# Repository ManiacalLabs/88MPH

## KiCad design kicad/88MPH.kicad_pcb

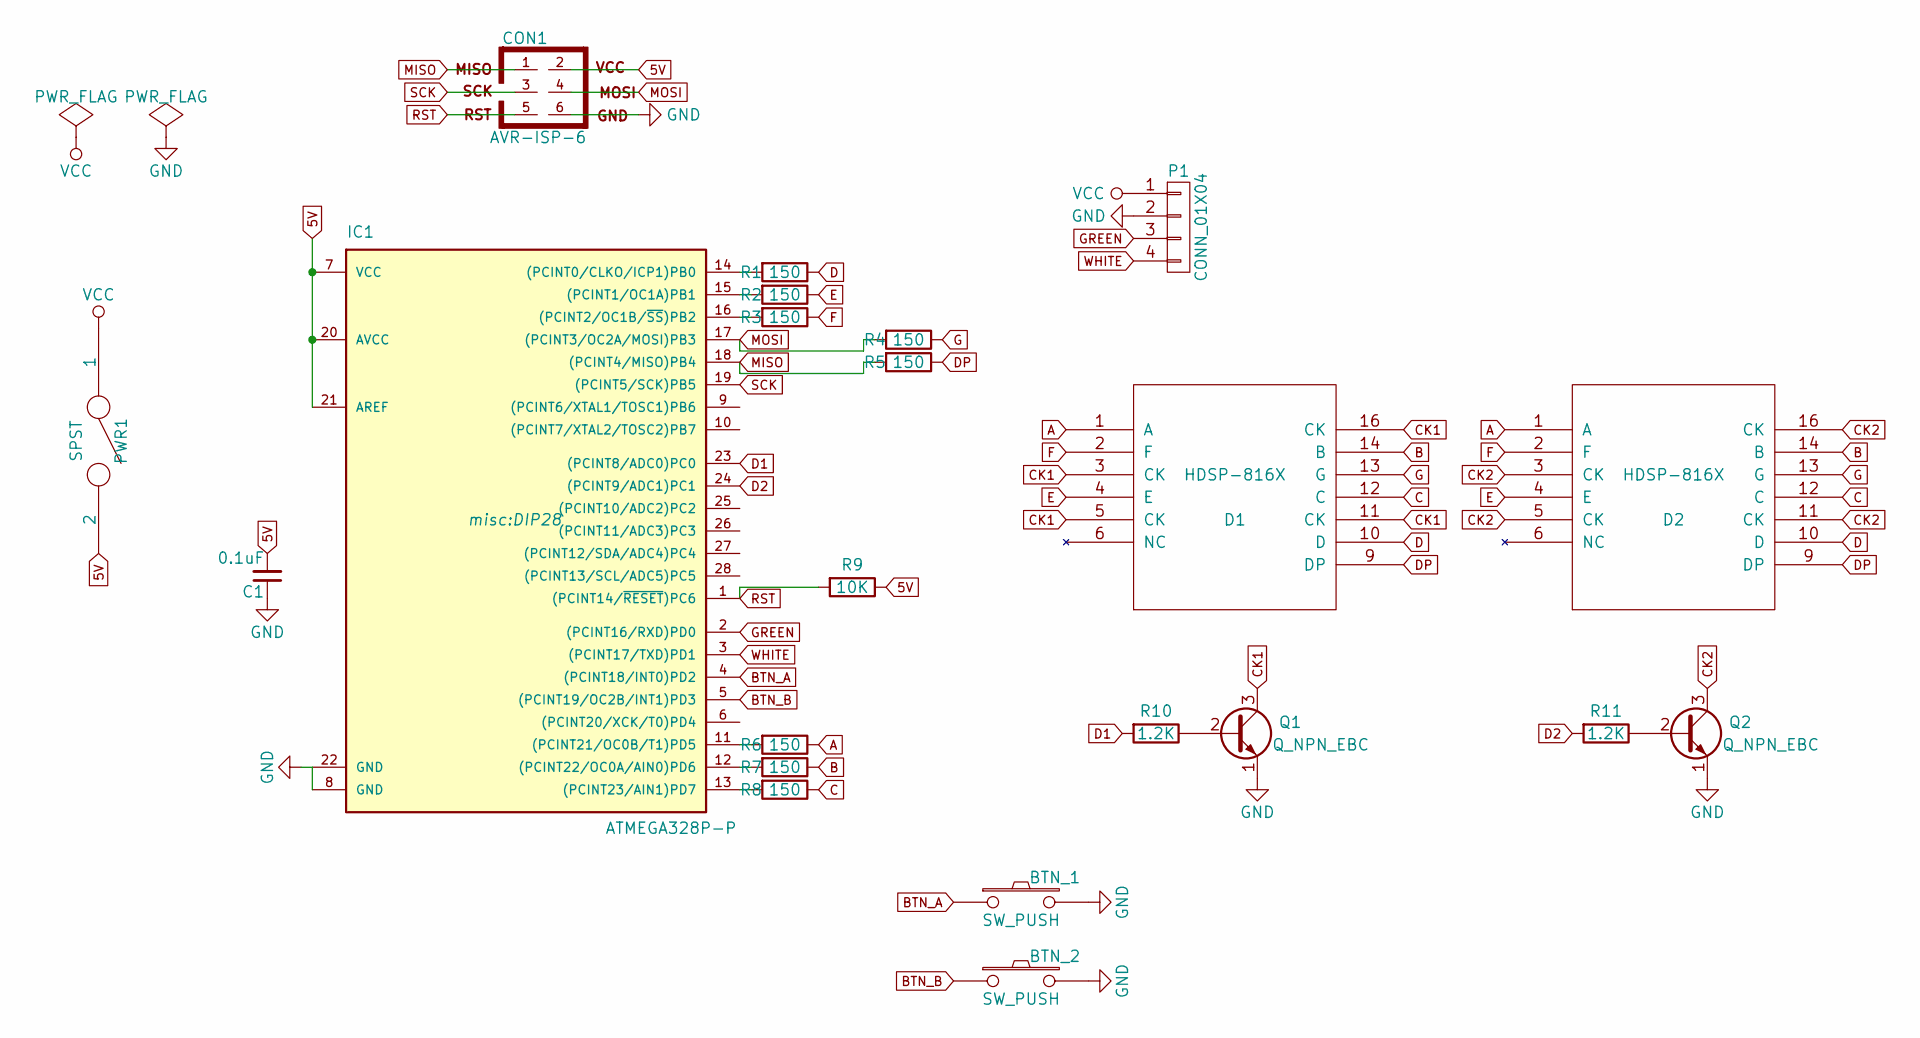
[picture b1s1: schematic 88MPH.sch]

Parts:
BTN_1, BTN_2: SW_PUSH; SW_PUSH_6mm
C1: 0.1uF; C_Disc_D3_P2.5
CON1: AVR-ISP-6; ICSP
D1, D2: HDSP-816X
IC1: ATMEGA328P-P; DIP28
P1: CONN_01X04; Strip_1x04
PWR1: SPST; SW_Micro_SPST
Q1, Q2: Q_NPN_EBC; TO-92_Inline_Narrow_Oval
R1, R2, R3, R4, R5, R6, R7, R8: 150; 0.125_Resistor
R9: 10K; 0.125_Resistor
R10, R11: 1.2K; 0.125_Resistor

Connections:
5V: C1.2, CON1.2, IC1.7 (VCC), IC1.20 (AVCC), IC1.21 (AREF), PWR1.2, R9.1
A: D1.1 (A), D2.1 (A), R6.1
B: D1.14 (B), D2.14 (B), R7.1
BTN_A: BTN_1.1, IC1.4 ((PCINT18/INT0)PD2)
BTN_B: BTN_2.1, IC1.5 ((PCINT19/OC2B/INT1)PD3)
C: D1.12 (C), D2.12 (C), R8.1
CK1: D1.3 (CK), D1.5 (CK), D1.11 (CK), D1.16 (CK), Q1.3 (C)
CK2: D2.3 (CK), D2.5 (CK), D2.11 (CK), D2.16 (CK), Q2.3 (C)
D: D1.10 (D), D2.10 (D), R1.1
D1: IC1.23 ((PCINT8/ADC0)PC0), R10.2
D2: IC1.24 ((PCINT9/ADC1)PC1), R11.2
DP: D1.9 (DP), D2.9 (DP), R5.1
E: D1.4 (E), D2.4 (E), R2.1
F: D1.2 (F), D2.2 (F), R3.1
G: D1.13 (G), D2.13 (G), R4.1
GND: BTN_1.2, BTN_2.2, C1.1, CON1.6, IC1.8 (GND), IC1.22 (GND), P1.2, Q1.1 (E), Q2.1 (E)
GREEN: IC1.2 ((PCINT16/RXD)PD0), P1.3
MISO: CON1.1, IC1.18 ((PCINT4/MISO)PB4), R5.2
MOSI: CON1.4, IC1.17 ((PCINT3/OC2A/MOSI)PB3), R4.2
unnamed: IC1.11 ((PCINT21/OC0B/T1)PD5), R6.2
unnamed: IC1.12 ((PCINT22/OC0A/AIN0)PD6), R7.2
unnamed: IC1.13 ((PCINT23/AIN1)PD7), R8.2
unnamed: IC1.14 ((PCINT0/CLKO/ICP1)PB0), R1.2
unnamed: IC1.15 ((PCINT1/OC1A)PB1), R2.2
unnamed: IC1.16 ((PCINT2/OC1B/~SS~)PB2), R3.2
unnamed: Q1.2 (B), R10.1
unnamed: Q2.2 (B), R11.1
RST: CON1.5, IC1.1 ((PCINT14/~RESET~)PC6), R9.2
SCK: CON1.3, IC1.19 ((PCINT5/SCK)PB5)
VCC: P1.1, PWR1.1
WHITE: IC1.3 ((PCINT17/TXD)PD1), P1.4

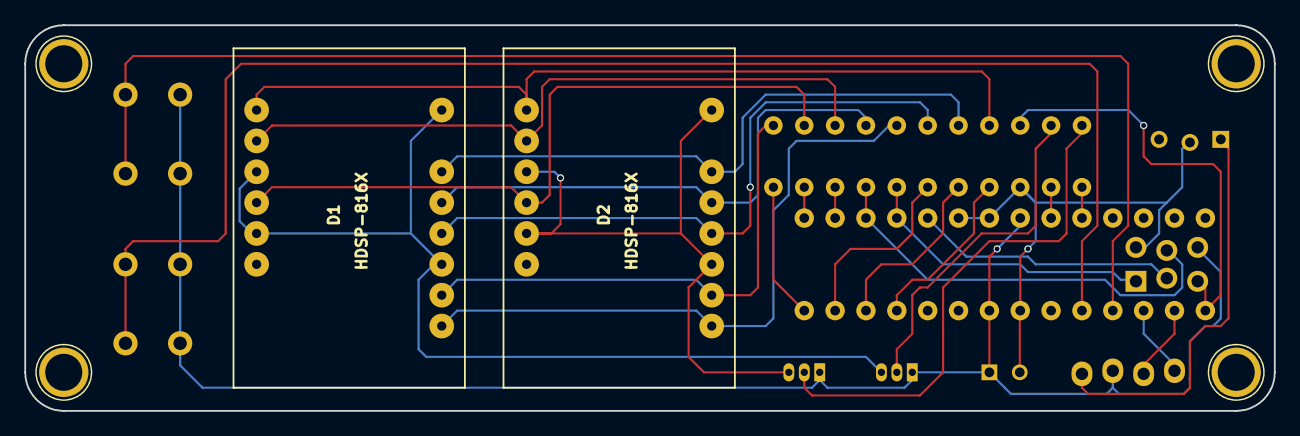
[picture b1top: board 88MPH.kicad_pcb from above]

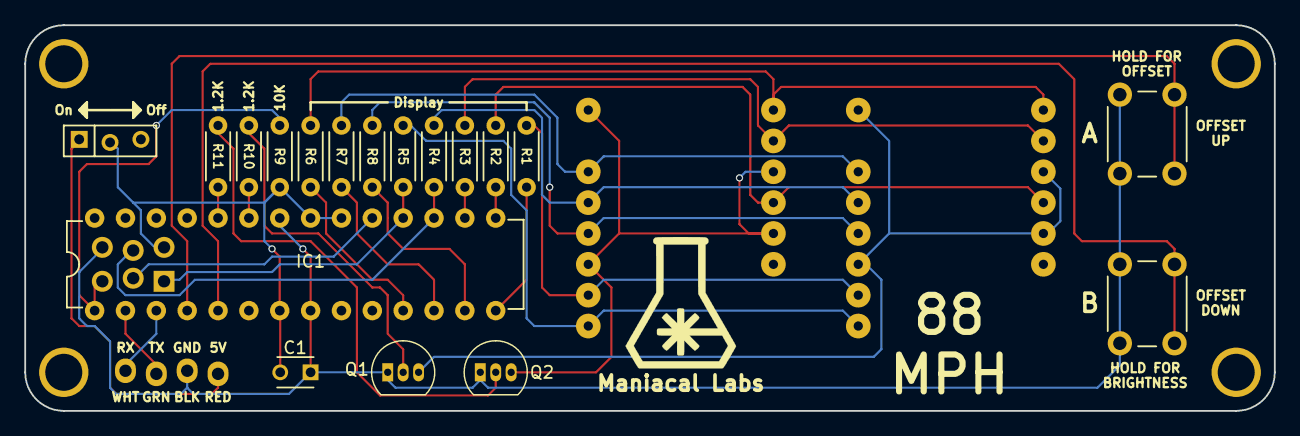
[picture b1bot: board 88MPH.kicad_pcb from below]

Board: 2 copper layers, 102.9 x 31.8 mm, 23 parts (20 on the bottom side), 31 nets.

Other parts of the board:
L103: Maniacal Labs; logo_MLlabs

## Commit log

2016-12-15 adding board definition
2016-12-15 starting firmware
2016-12-15 adding multiplexing and pwm
2016-12-15 adding button press
2016-12-16 working button hold logic
2016-12-16 more button funcs and example images
2016-12-17 working on buttons
2016-12-17 working buttons
2016-12-17 added waiting animation
2016-12-17 adding speed scaling and target reset
2016-12-18 grrr... arg! this was a bad idea...
2017-01-08 Completed Schematic
2017-01-08 Full layout
2017-01-08 gixed missing .lib files for Kicad
2017-01-08 Fixed cathode pin 3
2017-01-08 Removed pins 7, 8, and 15 from display footprint
2017-01-09 Cleanup of footprints and text
2017-01-10 Working firmware
2017-01-10 Fixed DP set on init
2017-01-10 Update LICENSE
2017-01-10 Create LICENSE
2017-01-23 minor fix for display order, deleted test dir
2017-01-29 adding bootloader
2017-02-04 reworked main loop and added sleep
